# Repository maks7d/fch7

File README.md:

# FCH7 - Flight Controller for Drone Quadcopter

##  Overview

FCH7 is a project aimed at developing a flight controller based on the STM32H743VITx MCU for drones with 4 to 8 motors, designed using KiCad.
The flight controller is in a 30x30mm form factor, with the goal of running it under Betaflight. It is for the moment only designed for DJI HD VTX.
> ** Project status:** This project is currently under development. The schematics are completed and the PCB is being routed.

##  Main Features

### Microcontroller
- **STM32H743VITx** - ARM Cortex-M7 dual core processor running at 480 MHz
  - 2048 KB Flash memory
  - 1024 KB RAM
  - 82 available GPIOs
  - LQFP100 package
  - 
### Embedded Sensors
- **ICM42688P** - Modern IMU (gyroscope + accelerometer)
- **MPU6500** - Secondary IMU for redundancy
- **QMC5883L** - 3-axis magnetometer for compass
- **SPL06-001** - Barometer for altitude

### Connectivity
- **ExpressLRS (ELRS)** - Integrated 2.4 GHz RF receiver
  - Dedicated RF_2.4 module
  - Support for long-range and low-latency link
- **USB-C** - 16-pin USB 2.0 connector for configuration and updates
- **HDGC1002WR Connectors** - Multiple connectors for peripherals
  - GPS (4 pins)
  - DJI HD VTX (6 pins)
  - Additional UART ports

### Power Supply
- **Intelligent power management**
  - **MP9943GQ-z** regulator - Main buck converter
  - **ME6217C33M5G** regulator - 3.3V LDO
  - Support pour batteries LiPo (VBAT)
  - Rails multiples: VDD_MCU, VDD_RECV, 4V5, VDD_GYRO

### Storage and LEDs
- **Blackbox** - SDIO interface for microSD card
  - Flight data logging for analysis
- **WS2812 LEDs** (addressable) - Programmable visual indicators
- **Status LEDs** - Multiple LEDs for diagnostics
##  Project Architecture

The project is organized into distinct hierarchical modules:

```
Folder Structure
C:.
│   .gitignore
│   fch7.kicad_pcb
│   fch7.kicad_prl
│   fch7.kicad_pro
│   fclib.bak
│   fclib.kicad_sym
│   fp-info-cache
│   fp-lib-table
│   README.md
│   sym-lib-table     
├───Hardware
│   ├───3D
│   │       CSTNE8M00G55Z000R0.stp
│   │       ICM-42688-P.stp
│   │       ME6217C33M5G.step
│   │       MP9943AGQ-Z.stp
│   │       MPU-6500.stp
│   │       STM32H743VIT6.stp
│   │
│   ├───Footprints
│   │   └───fch7_fp.pretty
│   │           AP2112K-1.8TRG1.kicad_mod
│   │           CONN-SMD_HDGC1002WR-S-6P.kicad_mod
│   │           CONN-SMD_HDGC1002WR-S-8P.kicad_mod
│   │           CRYSTAL-SMD_4P-L2.0-W1.6-BL.kicad_mod
│   │           CSNP1GCR01-BOW.kicad_mod
│   │           CSTNE8M00G55Z000R0.kicad_mod
│   │           IIM42352.kicad_mod
│   │           LED0603-R-RD_RED.kicad_mod
│   │           LGA-16_L3.0-W3.0-P0.50-BL_SQ.kicad_mod
│   │           LQFP-100_14x14mm_P0.5mm_STM32H743.kicad_mod
│   │           QFN40P300X300X95-25M-D.kicad_mod
│   │           RES-ARRAY-SMD_0603-8P-L3.2-W1.6-BL.kicad_mod
│   │           SENSOR-SMD_SPL06-001.kicad_mod
│   │           SM03B-SRSS-TB(LF)(SN).kicad_mod
│   │           SolderPad_1x01_SMD_2.2x1.6mm.kicad_mod
│   │           SON65P300X300X100-8N.kicad_mod
│   │           SOT23-5.kicad_mod
│   │           STM32H743VIT6.mod
│   │           SW-SMD_2P-TS24CA.kicad_mod
│   │           TSSOP-28_L9.7-W4.4-P0.65-LS6.4-BL-EP-2.kicad_mod
│   │           USB-C-SMD_TYPE-C-6PIN-2MD-073.kicad_mod
│   │           WIFIM-SMD_ESP-01F-2M.kicad_mod
│   │           WIRELM-SMD_E28-2G4M27SX.kicad_mod
│   └───Symbols
│       └───fch7_sym
│               CSTNE8M00G55Z000R0.bak
│               CSTNE8M00G55Z000R0.kicad_sym
│               fch7_sym.bak
│               fch7_sym.kicad_sym
│               ICM-42688-P.kicad_sym
│               ME6217C33M5G.bak
│               ME6217C33M5G.kicad_sym
│               MP9943AGQ-Z.bak
│               MP9943AGQ-Z.kicad_sym
│               MPU-6500.kicad_sym
│               STM32H743VIT6.kicad_sym
└───Schematic
        blackbox_led.kicad_sch
        connectors.kicad_sch
        ERC.rpt
        fch7.csv
        fch7.kicad_sch
        fp-info-cache
        MCU.kicad_sch
        Power.kicad_sch
        rf_rx.kicad_sch
        sensors.kicad_sch
        ~fch7.kicad_sch.lck
```

##  Custom Components

The project uses a custom symbol library (`fclib.kicad_sym`) containing:
- ICM42688P (IMU)
- MPU6500 (IMU)
- QMC5883L (Magnetometer)
- SPL06-001 (Barometer)
- elrs_rx (RF Modules)
- MP9943GQ-z (Buck converter)
- ME6217C33M5G (LDO)
- Connecteurs HDGC1002WR (4P, 6P, 8P)
- CSNP1GCR01-BOW
- WS2812_ (LEDS)

##  Applications

This flight controller is designed for:
- Freestyle drones
- Long-range drones
- Stabilized and acrobatic flight applications
- Compatibility with open-source firmwares (Betaflight)
- 
##  Technical Specifications

### Available Interfaces
- **SPI** - High-speed communication with sensors and OSD
- **I2C** - Communication with magnetometer and barometer
- **UART** - Multiple ports for GPS, telemetry, peripherals
- **SDIO** - SD card interface for blackbox
- **PWM/DShot** - Motor control (via MCU GPIO)
- **USB** - Configuration and firmware update

### Power Requirements
- Input: LiPo Batteries (2-6S typical)
- Regulated rails: 3.3V, 4.5V, VDD_MCU, VDD_RECV, VDD_GYRO
- Reverse polarity protection

##  Required Tools

### Software
- **KiCad 9.0** or higher - Schematic and PCB design
- **Git** - Version control
- 
##  Development Roadmap

- [x] MCU schematic
- [x] Power schematic
- [x] Sensors schematic
- [x] RF receiver schematic
- [x] Blackbox/LEDs schematic
- [x] Connectors schematic
- [x] Custom symbol library
- [x] PCB layout
- [ ] Track routing
- [ ] DRC/ERC verification
- [ ] Gerber file generation
- [ ] Prototype and testing
- [ ] Base firmware
- [ ] User documentation

##  Design Notes

##  Contribution

This project is under active development. Contributions, suggestions, and feedback are welcome !
##  Auteur

Maxim - [maks7d](https://github.com/maks7d)

### Communauté
- [ExpressLRS](https://www.expresslrs.org/) - ExpressLRS Documentation
- [KiCad Forum](https://forum.kicad.info/) - KiCad Support

---

**Version:** 0.1-alpha  
**Last Updated:** December 2025

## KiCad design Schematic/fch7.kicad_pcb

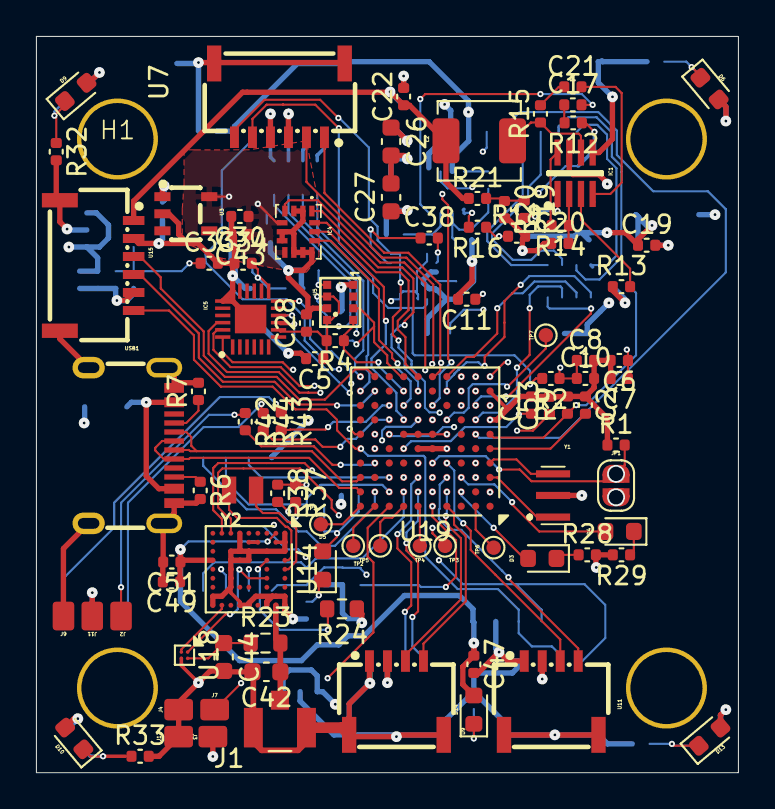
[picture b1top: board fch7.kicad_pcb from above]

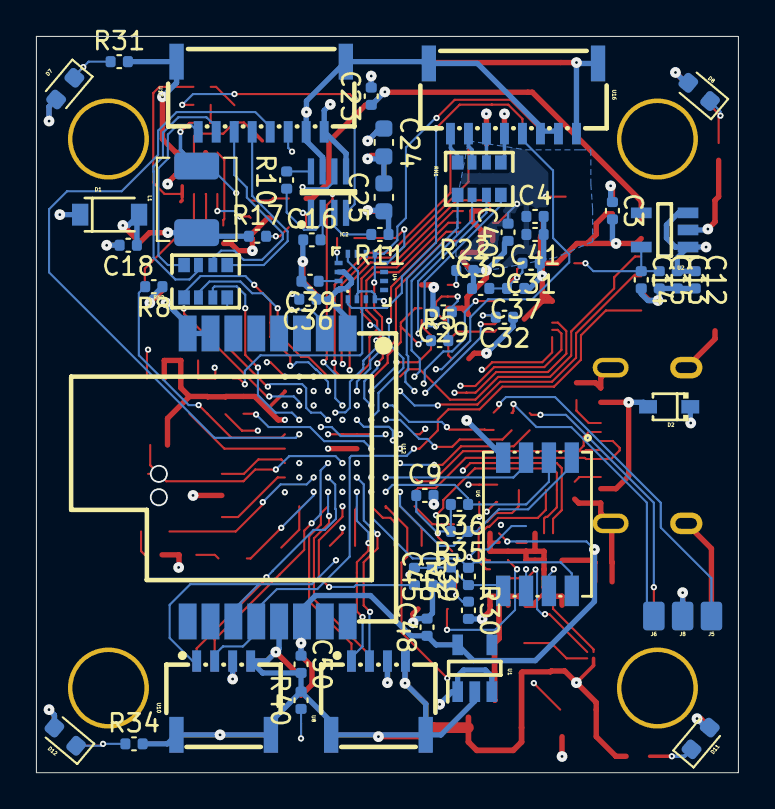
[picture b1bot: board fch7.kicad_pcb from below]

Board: 4 copper layers, 39.0 x 40.9 mm, 155 parts (61 on the bottom side), 125 nets.

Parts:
C1, C41, C43, C53: 2.2u; C_0402_1005Metric
C2, C5, C6, C7, C8, C9, C12, C14, C16, C17, C20, C21, C28, C29, C31, C32, C33, C34, C36, C40, C45, C47, C50: 100n; C_0402_1005Metric
C3, C4, C11: 1u; C_0402_1005Metric
C10, C39: 4.7u; C_0402_1005Metric
C13, C15, C18, C19, C22, C23, C48: 22u; C_0402_1005Metric
C24, C25, C26, C27: 47u; C_0603_1608Metric
C30, C35, C37, C46: 10n; C_0402_1005Metric
C38: 220n; C_0402_1005Metric
C42, C44: DNP; C_0603_1608Metric
C49: 10u; C_0402_1005Metric
C51: 0.1u; C_0402_1005Metric
D1: 1N5819W; SOD-123_L2.7-W1.6-LS3.7-RD
D2: BAT60B; SOD-323_L1.8-W1.3-LS2.5-RD
D3, D4, D5, D6, D7, D8, D9, D10, D11, D12, D13, D14: NCD0603R3; LED_0603_1608Metric
H1: MountingHole; MountingHole_quad_30.5x30.5
IC1, IC2: MP9943AGQ-Z; SON65P300X300X100-8N
IC4: ICM-42688-P; IIM42352
IC5: MPU-6500; QFN40P300X300X95-25M-D
J1: U.FL-R-SMT-1_01_; HIROSE_U.FL-R-SMT-1_01_
J2, J3, J4, J5, J6, J7, J8, J9, J11, J12: PIN2216; SolderPad_1x01_SMD_1.2x1.6mm
JP1: SolderJumper_2_Open; SolderJumper-2_P1.3mm_Open_RoundedPad1.0x1.5mm
L1, L2: 10u; L_Sunlord_MWSA0402S
R1, R8, R35, R36, R37, R38, R39: 10k; C_0402_1005Metric
R2, R3, R4, R5: 2.2k; C_0402_1005Metric
R6, R7: 5k1; C_0402_1005Metric
R9, R31, R32, R33, R34: 1k; C_0402_1005Metric
R10, R14, R22: 100k; C_0402_1005Metric
R11, R13: 1M; C_0402_1005Metric
R12, R15: 20; C_0402_1005Metric
R16, R19: 51k; C_0402_1005Metric
R17, R21: 41.2k; C_0402_1005Metric
R18: 6.98k; C_0402_1005Metric
R20: 3.92k; C_0402_1005Metric
R23: 0; R_0603_1608Metric
R24: 10k; R_0603_1608Metric
R28, R29, R30, R40: 470; C_0402_1005Metric
R42, R43, R44: 120; C_0402_1005Metric
RN1, RN2: 100; RES-ARRAY-SMD_0603-8P-L3.2-W1.6-BL
TP1, TP2, TP3, TP4, TP5, TP6, TP7: TestPoint; TestPoint_Pad_D0.8
U1, U2: ME6217C33M5G; SOT23-5
U3: LDO-1.8v; AP2112K-1.8TRG1
U4: QMC5883L; LGA-16_L3.0-W3.0-P0.50-BL_SQ
U5: SPL06-001; SENSOR-SMD_SPL06-001
U6: CSNP1GCR01-BOW
U7, U15: HDGC1002WR-S-6P; CONN-SMD_HDGC1002WR-S-6P
U8, U9, U10, U11: HDGC1002WR-S-4P; CONN-SMD_4P-P1.00_HDGC_HDGC1002WR-S-4P
U12: E28-2G4M27SX; WIRELM-SMD_E28-2G4M27SX
U14: MIA-M10Q; ublox_LGA-53_4.5x4.5mm_Layout9x9_P0.5mm
U16, U17: HDGC1002WR-S-8P; CONN-SMD_HDGC1002WR-S-8P
U18: MAX40200ANS; WLP-4_0.728x0.728mm_Layout2x2_P0.35mm
U19: STM32H743VIHx; TFBGA-100_8x8mm_Layout10x10_P0.8mm
USB1: USB-C-SMD_TYPE-C-6PIN-2MD-073
Y1: 8MHz; CSTNE8M00G55Z000R0
Y2: CM8V-T1A; XTAL_CM8V-T1A-32.768KHZ-7PF-20PPM-TB-QC

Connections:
5V: C3.1, C12.1, C13.1, D1.1 (K), D2.1 (K), D6.2 (A), D7.2 (A), D8.2 (A), D9.2 (A), D10.2 (A), D11.2 (A), D12.2 (A), D13.2 (A), J3.1, J8.1, J11.1, U1.1 (IN), U1.3 (CE), U2.1 (IN), U2.3 (CE), U3.1 (VIN), U7.4, U8.3, U9.2, U10.3, U11.2
5V5_BEC: C18.1, C19.1, D1.2 (A), L1.2, R17.1
5V_USB: D2.2 (A), USB1.2 (VBUS), USB1.11 (VBUS)
9V_BEC: C22.1, C23.1, L2.2, R21.1, U15.1
/Blackbox_led/LED0_R: D3.1 (K), R28.1
/Blackbox_led/LED1_R: D4.1 (K), R29.1
/Blackbox_led/LED_MCU_R: D5.1 (K), R30.1
/MCU/BOOT0: JP1.2 (B), R1.2, U19.D5 (BOOT0)
/MCU/CC1: R7.1, USB1.4 (CC1)
/MCU/CC2: R6.1, USB1.10 (CC2)
/MCU/NRST: C2.2, U19.E1 (NRST)
/MCU/OTG_FS+: U19.B10 (PA12), USB1.6 (DP1), USB1.8 (DP2)
/MCU/OTG_FS-: U19.C10 (PA11), USB1.5 (DN2), USB1.7 (DN1)
/MCU/PH0-OSC_IN: U19.C1 (PH0), Y1.1 (INPUT)
/MCU/PH1-OSC_OUT: U19.D1 (PH1), Y1.3 (OUTPUT)
/MCU/VCAP1: C1.1, U19.E7 (VCAP)
/MCU/VCAP2: C53.1, U19.F8 (VCAP)
/Power/FB_5V: IC2.1 (FB), R16.2
/Power/FB_9V: IC1.1 (FB), R19.2
/Power/LC_5V: IC2.6 (SW), L1.1, R12.1
/Power/LC_9V: IC1.6 (SW), L2.1, R15.1
/Sensors/C1: C39.1, U4.15 (C1)
/Sensors/REGOUT: C32.2, IC5.10 (REGOUT)
/Sensors/SETC: C38.2, U4.13 (SETC)
/Sensors/SETP: C38.1, U4.8 (SETP)
/connectors/PWM1: RN2.1, U17.8
/connectors/PWM2: RN2.2, U17.7
/connectors/PWM3: RN2.3, U17.6
/connectors/PWM4: RN2.4, U17.5
/connectors/PWM5: RN1.4, U16.5
/connectors/PWM6: RN1.3, U16.6
/connectors/PWM7: RN1.2, U16.7
/connectors/PWM8: RN1.1, U16.8
/rf_rx/GNSS_AMPLI: C44.1, R23.1, U18.A2 (OUT)
/rf_rx/LED_RECV: D14.1 (K), R40.1
/rf_rx/LNA: U14.H9 (LNA_EN), U18.B1 (EN)
/rf_rx/RESET_MIA: R24.2, U14.C4 (~RESET)
/rf_rx/RF_IN: C42.1, J1.SIG, R23.2, U14.B9 (RF_IN)
/rf_rx/VCC_RF: U14.C6 (VCC_RF), U18.A1 (VDD)
AIRS: TP7.1, U19.G4 (PC4)
BEEPER: J7.1, U19.A8 (PA15)
GND: C1.2, C2.1, C3.2, C4.2, C5.2, C6.2, C7.2, C8.2, C9.2, C10.2, C11.2, C12.2, C13.2, C14.2, C15.2, C16.1, C18.2, C19.2, C20.1, C22.2, C23.2, C24.2, C25.2, C26.2, C27.2, C28.2, C29.2, C30.2, C31.1, C32.1, C33.2, C34.1, C35.1, C36.1, C37.1, C39.2, C40.1, C41.1, C42.2, C43.2, C44.2, C45.1, C46.1, C47.2, C48.2, C49.2, C50.2, C51.2, C53.2, IC1.5 (GND), IC2.5 (GND), IC4.2 (RESV_1), IC4.3 (RESV_2), IC4.6 (GND), IC4.7 (RESV_3), IC4.9 (INT2_/_FSYNC_/_CLKIN), IC4.10 (RESV_4), IC4.11 (RESV_5), IC5.18 (GND_1), IC5.19 (RESV_1), IC5.25 (GND_2), J1.G1, J1.G2, J4.1, J9.1, J12.1, R1.1, R6.2, R7.2, R9.2, R18.2, R20.2, R22.2, R24.1, R28.2, R29.2, R30.2, R31.2, R32.2, R33.2, R34.2, R40.2, U1.2 (GND), U2.2 (GND), U3.2 (GND), U4.14 (GND), U4.16 (GND), U5.1 (GND), U5.6 (GND), U6.4 (VSS), U7.3, U7.7, U7.8, U8.4, U8.5, U8.6, U9.1, U9.5, U9.6, U10.4, U10.5, U10.6, U11.1, U11.5, U11.6, U12.1 (GND), U12.7 (GND), U12.8 (GND), U12.13 (GND), U14.A1 (GND), U14.A2 (GND), U14.A3 (GND), U14.A8 (GND), U14.A9 (GND), U14.B2 (GND), U14.B8 (GND), U14.C3 (GND), U14.C9 (GND), U14.E3 (GND), U14.E4 (GND), U14.E9 (GND), U14.F1 (GND), U14.F3 (GND), U14.F4 (GND), U14.F9 (Reserved), U14.G3 (GND), U14.G4 (GND), U14.G5 (GND), U14.G6 (GND), U14.G7 (Reserved), U14.H8 (GND), U14.J8 (GND), U14.J9 (GND), U15.2, U15.5, U15.7, U15.8, U16.1, U16.10, U17.1, U17.9, U18.B2 (GND), U19.C2 (VSS), U19.E4 (VSS), U19.E5 (VSS), U19.E6 (VSS), U19.G1 (VSSA), U19.J1 (VSS), USB1.1 (GND), USB1.12 (GND), USB1.13 (SHELL), USB1.14 (SHELL), Y1.2 (GND)
I2C1_SCL: R2.2, U4.1 (SCL), U7.5, U19.B5 (PB6)
I2C1_SDA: R3.2, U4.9 (SDA), U7.6, U19.A5 (PB7)
I2C2_SCL: R4.1, U5.4 (SCK), U19.J7 (PB10)
I2C2_SDA: R5.1, U5.3 (SDA), U19.K7 (PB11)
IMU1_SPI4_EXTI2: IC4.4 (INT1_/_INT), U19.H6 (PE11)
IMU2_SPI1_EXTI1: IC5.12 (INT), U19.G5 (PB2)
LED_0: D3.2 (A), U19.B3 (PE3)
LED_1: D4.2 (A), U19.C3 (PE4)
NRESET_RECV: U12.2 (NRESET), U19.C7 (PD3)
unnamed: C17.1, R12.2
unnamed: C21.1, R15.2
unnamed: D6.1 (K), D7.1 (K), R31.1
unnamed: D8.1 (K), D9.1 (K), R32.1
unnamed: D10.1 (K), D11.1 (K), R33.1
unnamed: D12.1 (K), D13.1 (K), R34.1
unnamed: C21.2, IC1.4 (BST)
unnamed: IC1.3 (EN/SYNC), R13.2
unnamed: IC1.8 (PG), R14.2
unnamed: C20.2, IC1.2 (VCC), R14.1
unnamed: C17.2, IC2.4 (BST)
unnamed: IC2.3 (EN/SYNC), R11.2
unnamed: IC2.8 (PG), R10.2
unnamed: C16.2, IC2.2 (VCC), R10.1
unnamed: J2.1, R42.1
unnamed: J5.1, R43.1
unnamed: J6.1, R44.1
unnamed: R16.1, R17.2, R18.1
unnamed: R19.1, R20.1, R21.2
unnamed: R22.1, U5.8 (SDO)
unnamed: U14.A4 (RTC_I), Y2.2
unnamed: U14.A5 (RTC_O), Y2.1
unnamed: U14.D2 (Reserved), U14.E2 (Reserved)
PWM_1: RN2.8, U19.J4 (PB0)
PWM_2: RN2.7, U19.K4 (PB1)
PWM_3: RN2.6, U19.G2 (PA0)
PWM_4: RN2.5, U19.H2 (PA1)
PWM_5: RN1.5, U19.J2 (PA2)
PWM_6: RN1.6, U19.K2 (PA3)
PWM_7: RN1.7, U19.K10 (PD12)
PWM_8: RN1.8, U19.J10 (PD13)
PWM_9: R43.2, U19.H8 (PD14)
PWM_10: R44.2, U19.G8 (PD15)
PWM_SW_2812: R42.2, U19.D9 (PA8)
SDIO_CLK: U6.3 (SCLK), U19.C8 (PC12)
SDIO_CMD: R39.2, U6.8 (CMD), U19.B7 (PD2)
SDIO_D0: R38.2, U6.7 (SDD0), U19.F9 (PC8)
SDIO_D1: R37.2, U6.6 (SDD1), U19.E9 (PC9)
SDIO_D2: R35.1, U6.1 (SDD2), U19.B9 (PC10)
SDIO_D3: R36.1, U6.2 (CD/SDD3), U19.B8 (PC11)
SENS_CUR1: U17.4, U19.F2 (PC1)
SENS_CUR2: U16.4, U19.K3 (PA7)
SENS_VOL: R8.2, R9.1, U19.F1 (PC0)
SPI1_IMU1_CS: IC5.22 (NCS), U19.B1 (PC15)
SPI1_MISO: IC5.9 (SDO_/_AD0), U19.J3 (PA6)
SPI1_MOSI: IC5.24 (SDA_/_SDI), U19.D6 (PD7)
SPI1_SCLK: IC5.23 (SCL_/_SCLK), U19.H3 (PA5)
SPI3_IMU3_CS: TP6.1, U19.A2 (PC13)
SPI3_MISO: TP4.1, U19.A6 (PB4)
SPI3_MOSI: TP3.1, U19.C5 (PB5)
SPI3_SCLK: TP5.1, U19.A7 (PB3)
SPI4_IMU2_CS: IC4.12 (AP_CS), U19.H7 (PE15)
SPI4_MISO: IC4.1 (AP_SDO_/_AP_AD0), U19.J6 (PE12)
SPI4_MOSI: IC4.14 (AP_SDA_/_AP_SDIO_/_AP_SDI), U19.K6 (PE13)
SPI4_SCLK: IC4.13 (AP_SCL_/_AP_SCLK), U19.G7 (PE14)
SWD_SWCLK: TP2.1, U19.A9 (PA14)
SWD_SWDIO: TP1.1, U19.A10 (PA13)
UART1_RX: U7.1, U14.H1 (RX), U19.K5 (PE9)
UART1_TX: U7.2, U14.G1 (TX), U19.G6 (PE10)
UART2_RX: U8.2, U19.C6 (PD6)
UART2_TX: U8.1, U19.B6 (PD5)
UART3_RX: U15.4, U19.J9 (PD9)
UART3_TX: U15.3, U19.K9 (PD8)
UART4_RX: U9.3, U19.B4 (PB8)
UART4_TX: U9.4, U19.A4 (PB9)
UART6_RX: U10.2, U12.12 (MISO_TX), U15.6, U19.E10 (PC7)
UART6_TX: U10.1, U12.11 (MOSI_RX), U19.F10 (PC6)
UART7_RX: U17.3, U19.H5 (PE7)
UART8_RX: U11.3, U19.D4 (PE0)
UART8_TX: U11.4, U19.C4 (PE1)
VBAT: C24.1, C25.1, C26.1, C27.1, IC1.7 (IN), IC2.7 (IN), R8.1, R11.1, R13.1, U16.2, U16.3, U16.9, U17.2, U17.10
VCC_ICM: C4.1, C30.1, C40.2, C41.2, C43.1, IC4.5 (VDDIO), IC4.8 (VDD), U3.5 (VOUT)
VDD_MCU: C5.1, C6.1, C7.1, C8.1, C9.1, C10.1, C11.1, C14.1, C15.1, C28.1, C29.1, C31.2, C33.1, C34.2, C35.2, C36.2, C37.2, C45.2, C46.2, D5.2 (A), IC5.8 (VDDIO), IC5.13 (VDD), JP1.1 (A), R2.1, R3.1, R4.2, R5.2, R35.2, R36.2, R37.1, R38.1, R39.1, U2.5 (OUT), U4.2 (VDD), U4.4 (S1), U4.12 (VDDIO), U5.5 (VDD), U5.7 (VDDIO), U6.5 (VCC), U19.D2 (VDD), U19.F4 (VDDLDO), U19.F5 (VDD), U19.F6 (VDD33_USB), U19.F7 (PDR_ON), U19.H1 (VDDA), U19.K1 (VDD)
VDD_RECV: C47.1, C48.1, C49.1, C50.1, C51.1, D14.2 (A), U1.5 (OUT), U12.14 (VCC), U14.B1 (VCC), U14.J4 (V_IO)

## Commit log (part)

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2025-11-15 init
2025-11-17 update : pin stm32 connections
2025-11-17 finished MCU sheet and start hierarchy sheets for other components
2025-11-17 started Power page
2025-11-18 finished -power and sensors page, started OSD
2025-11-19 finished blackbox led and osd, then started rx
2025-11-20 finshed every schematic pages, remains footprints assignments
2025-11-20 Refactor code structure for improved readability and maintainability
2025-11-23 refactor labels U and assigned resistance footprint
2025-11-23 refactor and update references, added some footprints
2025-11-24 refactor and add footprints for almost every component
2025-11-24 schematic fully finished, every footprint assigned, still electrical checking to do
2025-11-25 reviewing and refactoring footprints and full schematic
2025-11-25 Update schematic and footprint libraries with various component modifications
    - Updated fp-info-cache with new component details and footprint changes.
    - Modified osd.kicad_sch to correct pin types and add no_connect entries.
    - Adjusted rf_rx.kicad_sch to fix pin assignments and update component properties.
    - Enhanced sensors.kicad_sch with new properties for QMC5883L and SPL06-001 sensors.
    - Added new libraries to sym-lib-table and fp-lib-table for better organization and access to components.
2025-11-26 Refactor fp-lib-table: Remove unused libraries and update description for fch7_fp
2025-11-27 Refactor schematic files and update component placements
    - Adjusted component positions in osd.kicad_sch for better layout.
    - Added new junctions and wires in rf_rx.kicad_sch to improve connectivity.
    - Introduced additional junctions and wires in sensors.kicad_sch for enhanced signal routing.
    - Removed outdated backup file fch7-2025-11-18_191836.zip and added new backup fch7-2025-11-27_202230.zip.
2025-11-28 Removed useless analog OSD and VTX conneections to support only digital DJI
2025-11-29 refactor : improve readability and portability of the project
2025-11-29 refactor: update README for clarity and accuracy in project description
2025-11-29 zdd :minor improvements
2025-12-01 Refactor mounting hole footprints and update schematic
    - Deleted obsolete mounting hole footprints from the PCB design.
    - Introduced a new footprint "MountingHole_quad_30.5x30.5" for improved layout.
    - Updated references in the schematic to use the new mounting hole footprint.
    - Adjusted positions of mounting hole symbols in the schematic for better alignment.
    - Changed pin types for USB VBUS connections from "power_out" to "bidirectional" for accurate functionality.
    - Cleaned up the footprint information cache to reflect the new footprint changes.
2025-12-02 Update component properties for RF receiver schematic
    - Changed the "Value" and "MPN" properties of components in the rf_rx.kicad_sch file from "E28-2G4M27SX" to "ESP-01F-2M".
    - Reversed the previous changes for the same properties, updating them back to "E28-2G4M27SX".
2025-12-02 Add new footprints for SOD-123 and SOD-323 components
2025-12-02 Update fp-info-cache with new component values and add SOD-123 and SOD-323 footprints
2025-12-03 place every big component on pcb
2025-12-04 Update clearance and width parameters in fch7.kicad_pro
    - Increased min_clearance from 0.0 to 0.2 for improved design rules.
    - Set min_track_width from 0.0 to 0.2 to enhance track integrity.
    - Adjusted min_via_diameter from 0.5 to 0.8 for better via performance.
    - Updated via_drill size from 0.3 to 0.4 for improved manufacturability.
    - Added new differential pair settings for GND and POWER with specific parameters for clearance, track width, and via dimensions.
    - Changed net_format_name to "KiCad" for better compatibility.
2025-12-05 still progressing on placing capacitance
2025-12-05 finised capacitor placement
2025-12-05 progress on placing components
2025-12-07 finished components placement
2025-12-08 Refactor schematic files and add net definitions
    - Updated priority values for GND and POWER net classes in fch7.kicad_pro.
    - Added USB_DIFF net class with associated patterns for USB differential signals.
    - Removed duplicate junctions and adjusted wire connections in rf_rx.kicad_sch for clarity.
    - Adjusted component positions and properties in rf_rx.kicad_sch for better layout.
    - Modified text positions for IMU components in sensors.kicad_sch to improve readability.
    - Cleaned up unnecessary wires and added new connections in sensors.kicad_sch.
2025-12-08 Update global label for SDIO and modify wire connections in blackbox LED schematic
2025-12-09 Adjust USB differential pair clearance in fch7.kicad_pro from 0.6 to 0.2
2025-12-10 Update fp-info-cache with new identifier for Reverb_BTDR-1H module
2025-12-10 Update 3D model paths in PCB design and modify fp-info-cache
    - Changed model paths for several components in fch7.kicad_pcb to absolute paths for better accessibility.
    - Added new 3D models for components including CSNP1GCR01-BOW, GoertekSPL06-001, and USB-C standard.
    - Updated UUIDs for some components to maintain consistency.
    - Updated the fp-info-cache with a new hash for the Audio_Module footprint.
2025-12-11 Add 3D models for various components and update UUIDs in PCB design
    - Added 3D model for AP2112K-1.8TRG1 with appropriate offset, scale, and rotation.
    - Updated UUID for a pad in the footprint of a component.
    - Added 3D model for ESP-01F with specified offset, scale, and rotation.
    - Added 3D model for QMC5883L with adjusted offset, scale, and rotation.
    - Added 3D model for E28-2G4M27SX with defined offset, scale, and rotation.
    - Updated UUID for another pad in the footprint of a component.
2025-12-11 Update schematic parameters and footprint information
    - Modified differential pair dimensions to include a default gap, via gap, and width set to 0.0.
    - Updated track widths to include a default value of 0.0.
    - Added via dimensions with diameter and drill size set to 0.0.
    - Adjusted track width for netclass settings, changing values for specific netclasses.
    - Added new netclass entries for GND and POWER with corresponding patterns.
    - Updated footprint info cache with a new identifier for the Audio Module.
2025-12-12 Update schematic parameters and netclass definitions
    - Reduced minimum via diameter from 0.8mm to 0.6mm for improved design flexibility.
    - Removed redundant GND netclass configuration and adjusted POWER netclass priority.
    - Added additional POWER netclasses for better organization and routing.
    - Updated fp-info-cache with a new hash for the Audio_Module footprint.
2025-12-13 Refactor code structure and remove redundant sections for improved readability
2025-12-14 Translate README.md to English and update project details for clarity and consistency
2025-12-14 Remove USB differential pair settings from schematic configuration and update footprint info cache for Audio_Module.
2025-12-14 Added power zones in Inner2.cu layer for better power management
2025-12-15 still routing and defining plan zones for power nets
2025-12-16 Still routing and reordering components
2025-12-16 Still routing...
2025-12-19 Remove obsolete PCB file fch7.kicad_pcb
2025-12-19 refactoring pcb layout
2025-12-19 Refactoring and making some place for dual gyro on PCB
2025-12-20 Repositioned ICM for better routing, still MPU to place and route
2025-12-20 Remove outdated backup ZIP file from schematic directory
2025-12-20 minor update
2025-12-20 Re-introduced MPU6500, every component in place with their 3d model, every track is routed
2025-12-20 refactoring routing
2025-12-21 update routing
2025-12-21 finished every routing and fix errors in DRC
2025-12-22 Update 3D models and cache information for various components
    - Updated the cache ID for the Audio_Module to a new value.
    - Added 3D models for AP2112K-1.8TRG1, CSNP1GCR01-BOW, CSTNE8M00G55Z000R0, IIM42352, LGA-16, QFN40P300X300X95-25M-D, and others with correct file paths.
    - Changed file paths from Windows-style to Unix-style for consistency across the project.
    - Adjusted offsets, scales, and rotations for several models to ensure proper alignment in the schematic.
2025-12-22 minor update on label silkscreen
2025-12-28 Update schematic and footprint files for fch7 project
    - Adjusted minimum text height and thickness in fch7.kicad_pro for improved readability.
    - Replaced outdated components in fp-info-cache with new battery clip and various ICs, including AP2112K-1.8TRG1 and MPU-6500.
    - Updated the footprint library path in fp-lib-table to use an environment variable for better portability.
2025-12-29 Update schematic properties and model paths - Added MPN and Manufacturer properties for ICM-42688-P and MPU-6500 in sensors.kicad_sch. - Changed model paths to use the ${FCH7_3DMODEL_DIR} variable fo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
2025-12-30 compacting in 40mm wide format the board
2025-12-30 refactor pcb layout
2025-12-31 Update schematic and footprint files for various components
    - Adjusted minimum copper edge clearance in fch7.kicad_pro from 0.5 to 0.35.
    - Updated fp-info-cache with a new UUID for the Battery component.
    - Modified the 3D model offset for CONN-SMD_4P-P1.00_HDGC_HDGC1002WR-S-4P.
    - Changed the silk screen details for LGA-16_L3.0-W3.0-P0.50-BL_SQ, including repositioning the fp_circle and updating the reference text location.
    - Removed unnecessary silk screen lines and polygons from SOD-123_L2.7-W1.6-LS3.7-RD.
    - Adjusted the silk screen lines for USB-C-SMD_TYPE-C-6PIN-2MD-073, including repositioning and swapping UUIDs.
2025-12-31 update schematic after reviewing some footprints
2026-01-05 minor update and some checking
2026-01-06 pcb layout refactoring
2026-01-08 remove switch to use jumper for bootloader activation
2026-01-10 optimisation : - refactoring two 4 pin connector for mag and gps into one 6 pin connector - increased output voltage from 5V buck regulator to take into account voltage decrease schottky diodes
2026-01-14 switched mcu package to use TFBGA-100 8x8mm (stm32h743vih6)
2026-01-28 update routing and constraints according to jlcpcb specs
2026-01-28 update on routing
2026-01-29 fix: update fch7 library path and description in fp-lib-table
    - Changed the URI for the fch7 library to use the KIPRJMOD variable for better project portability.
    - Updated the description to specify that it contains footprints for fch7.
2026-01-29 Refactor organization repo
2026-01-29 Implement feature X to enhance user experience and optimize performance
2026-01-29 Add new footprint for WIRELM-SMD_E28-2G4M27SX with detailed specifications and pads
2026-01-29 Remove obsolete footprint WIRELM-SMD_E28-2G4M27SX and update library reference in fp-lib-table to fch7
2026-01-29 fix: update 3D model paths for various footprints to correct directory structure
2026-01-29 Update schematic files and footprint references
    - Updated the footprint reference in `fp-info-cache` for various components to use "fch7" instead of "fch7_fp".
    - Added a new 3D library reference for "fch7_3d" in `fp-lib-table`.
    - Introduced a new symbol for the RF GPS module "MIA-M10Q" in `rf_rx.kicad_sch`, including properties such as footprint, datasheet, and description.
    - Added multiple pins for the "MIA-M10Q" symbol with unique UUIDs.
    - Corrected the URI for the `fclib` in `sym-lib-table` to point to the correct project path.
2026-01-30 update routing and add MIA-M10Q
2026-01-30 fix: update library URI for fch7 footprint in fp-lib-table
    Changed the URI for the fch7 library from a relative path to a defined variable for better path management. This improves the portability of the project across different environments.
2026-01-30 update: refine component labels for IMU and Magnetometer in schematic
2026-01-31 Fix junction and wire positions in schematic; update capacitor and ground symbol properties
2026-02-08 Minor refactor
2026-02-12 update schematic diagram
2026-02-18 fix routing on RN2
2026-02-18 update: modify net connections and add unconnected nets in PCB design
